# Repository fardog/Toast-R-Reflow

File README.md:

# Toast-R-Reflow

This is a fork of [nsayer/Toast-R-Reflow][fork] but:

* Only the Controller II is supported
* Firmware builds with [PlatformIO][]
* Eagle files converted to KiCAD (untested, unfixed, and definitely missing
  things)

[fork]: https://github.com/nsayer/Toast-R-Reflow
[PlatformIO]: https://platformio.org/

I take credit for none of this; it's just more convenient for me to make changes
to the firmware this way, and the only reason I converted the hardware to KiCAD
is because that's what I had available to view them.

Included here is what it'll take to get firmware building and uploading using
this repo. The [original README][] has been moved to `README-original.md`.

Just don't blame me if you donk your board; I don't know what I'm doing.

[original README]: ./README-original.md

## Preparing for custom firmware

It's easiest to use PlatformIO once the board can be detected as an Arduino, so
you'll need to burn a bootloader.

What's required to do so isn't outlined in detail here, but here's what you'll
need to know:

* The ICSP header is the blue header on the back of the unit; listed as `JP4`,
  near the open-source hardware logo
* Its pinout is the usual ICSP layout; left-to-right, top-to-bottom:
  * Reset
  * SCK
  * MISO
  * GND
  * MOSI
  * VCC (5v)
* It runs an Atmega328PB, and is 5v tolerant
* I used an Arduino Micro as an ISP without issue, with reset wired to digital
  pin 10

The original README says that the board would work fine if you pretend it's an
Arduino UNO; that just didn't work for me given that board is an Atmega328P, and
this is an Atmega328PB. I read they're maybe mostly compatible but without
finding anything difinitive there, I got it working as the PB model.

For a bootloader that supports the Atmega328PB, use [MiniCore][]. Follow its
instructions to burn the loader; I used settings:

* Board: MiniCore -> Atmega328
* Clock: External 16 MHz
* BOD: BOD2.7V
* EEPROM: EEPROM retained
* Compiler LTO: LTO disabled
* Variant: 328PB
* Bootloader: Yes (UART0)

[MiniCore]: https://github.com/MCUdude/MiniCore

## FTDI Header

The board has a 6-pin inline header labeled "FTDI" which can be used for
programming, but you need to solder the jumper pins (labeled `SJ1`) to activate
the reset line. In my case, it was also missing a 0.1uF capacitor `C10` on the
line, but I have to assume that's not a common error.

## Building Custom Firmware

The `platformio.ini` in this repo is set up correctly; building and uploading
the firmware should work without additional settings.

## Changes to the firmware

* `SiO2` profile for drying silica gel; 110°C for 3hr

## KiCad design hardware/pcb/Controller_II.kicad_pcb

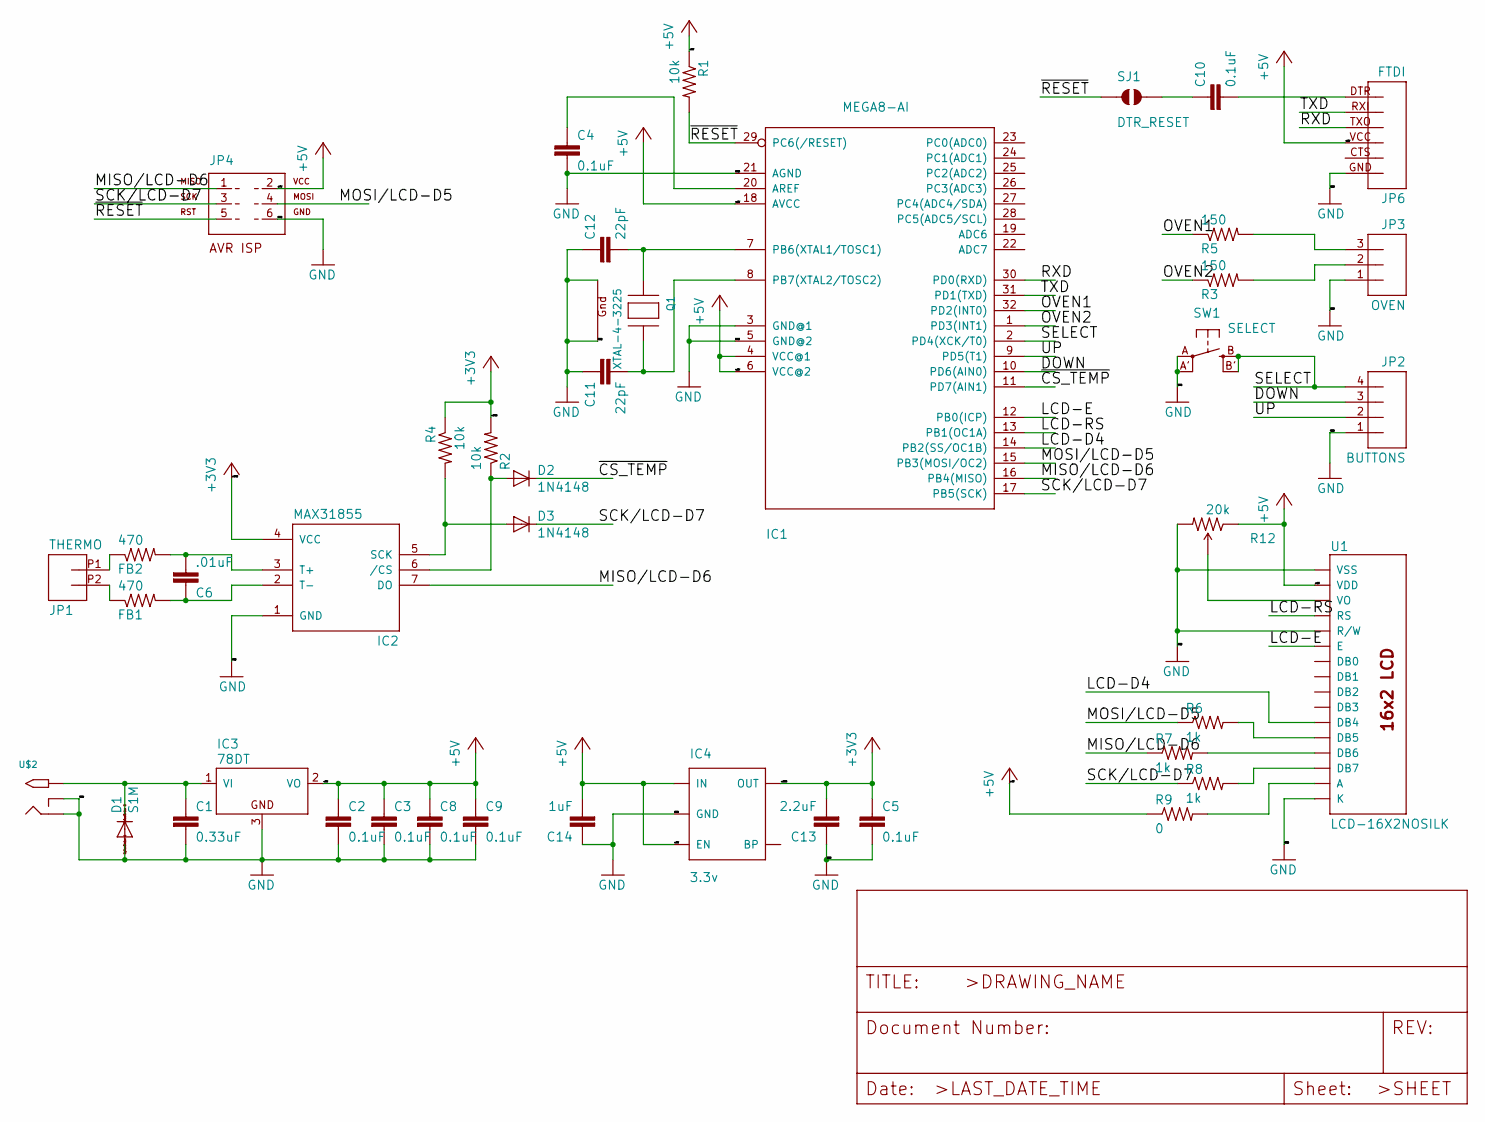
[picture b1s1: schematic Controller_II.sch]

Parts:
C1: 0.33uF; 0805
C2, C3, C4, C5, C8, C9, C10: 0.1uF; 0805
C6: .01uF; 0805
C11, C12: 22pF; 0805
C13: 2.2uF; 0805
C14: 1uF; 0805
D1: S1M; DO-214AC
D2, D3: 1N4148; SOD-323
FB1, FB2: 470; 0805
IC1: MEGA8-AI; TQFP32-08
IC2: MAX31855; SO08
IC3: 78DT; TO252
IC4: 3.3v; SOT23-5
JP1: THERMO; 1X02_2.54_SCREWTERM
JP2: BUTTONS; 1X04
JP3: OVEN; SCREWTERMINAL-5MM-3
JP4: ISP; AVR-ISP-6
JP6: FTDI; FTDI_BASIC
Q1: XTAL-4-3225; NX3225
R1, R2, R4: 10k; 0805
R3, R5: 150; 0805
R6, R7, R8: 1k; 0805
R9: 0; 0805
R12: 20k; TRIMPOT-3MM
SJ1: DTR_RESET; SJ_2S-NO
SW1: SELECT; EVQ-Q2
U1: LCD-16X2NOSILK; LCD-16X2_NOSILK
U$2: 2.1MMJACKSMT; DCJACK_2MM_SMT

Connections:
+3V3: C5.1, C13.2, IC2.4 (VCC), IC4.5 (OUT), R2.2, R4.1
+5V: C2.1, C3.1, C8.1, C9.1, C14.2, IC1.4 (VCC@1), IC1.6 (VCC@2), IC1.18 (AVCC), IC3.2 (VO), IC4.1 (IN), IC4.3 (EN), JP4.2, JP6.VCC (4), R1.1, R9.1, R12.1 (CCW), U1.2 (VDD)
/DOWN: IC1.10 (PD6(AIN0)), JP2.3
/LCD-D4: IC1.14 (PB2(SS/OC1B)), U1.11 (DB4)
/LCD-E: IC1.12 (PB0(ICP)), U1.6 (E)
/LCD-RS: IC1.13 (PB1(OC1A)), U1.4 (RS)
/MISO/LCD-D6: IC1.16 (PB4(MISO)), IC2.7 (DO), JP4.1, R7.1
/MOSI/LCD-D5: IC1.15 (PB3(MOSI/OC2)), JP4.4, R6.1
/OVEN1: IC1.32 (PD2(INT0)), R5.1
/OVEN2: IC1.1 (PD3(INT1)), R3.1
/RXD: IC1.30 (PD0(RXD)), JP6.TXO (3)
/SCK/LCD-D7: D3.1 (C), IC1.17 (PB5(SCK)), JP4.3, R8.1
/SELECT: IC1.2 (PD4(XCK/T0)), JP2.4, SW1.B (S), SW1.B' (S1)
/TXD: IC1.31 (PD1(TXD)), JP6.RXI (2)
/UP: IC1.9 (PD5(T1)), JP2.2
/~CS_TEMP: D2.1 (C), IC1.11 (PD7(AIN1))
/~RESET: IC1.29 (PC6(/RESET)), JP4.5, R1.2, SJ1.1
GND: C1.2, C2.2, C3.2, C4.2, C5.2, C8.2, C9.2, C11.1, C12.1, C13.1, C14.1, D1.A, IC1.3 (GND@1), IC1.5 (GND@2), IC1.21 (AGND), IC2.1 (GND), IC3.3 (GND), IC4.2 (GND), JP2.1, JP3.1, JP4.6, JP6.GND (6), Q1.2 (G2), Q1.4 (G1), R12.3 (CW), SW1.A, SW1.A' (P1), U1.1 (VSS), U1.5 (R/W), U1.16 (K), U$2.GND (RING), U$2.GNDBREAK (RING_SW)
unnamed: C1.1, D1.C, IC3.1 (VI), U$2.PWR1 (TIP), U$2.PWR2 (TIP)
unnamed: C4.1, IC1.20 (AREF)
unnamed: C6.1, FB1.2, IC2.2 (T-)
unnamed: C6.2, FB2.2, IC2.3 (T+)
unnamed: C10.1, SJ1.2
unnamed: C10.2, JP6.DTR (1)
unnamed: C11.2, IC1.8 (PB7(XTAL2/TOSC2)), Q1.3 (X2)
unnamed: C12.2, IC1.7 (PB6(XTAL1/TOSC1)), Q1.1 (X1)
unnamed: D2.2 (A), IC2.6 (/CS), R2.1
unnamed: D3.2 (A), IC2.5 (SCK), R4.2
unnamed: FB1.1, JP1.P2 (2)
unnamed: FB2.1, JP1.P1 (1)
unnamed: JP3.2, R3.2
unnamed: JP3.3, R5.2
unnamed: R6.2, U1.12 (DB5)
unnamed: R7.2, U1.13 (DB6)
unnamed: R8.2, U1.14 (DB7)
unnamed: R9.2, U1.15 (A)
unnamed: R12.2 (WIPER), U1.3 (VO)

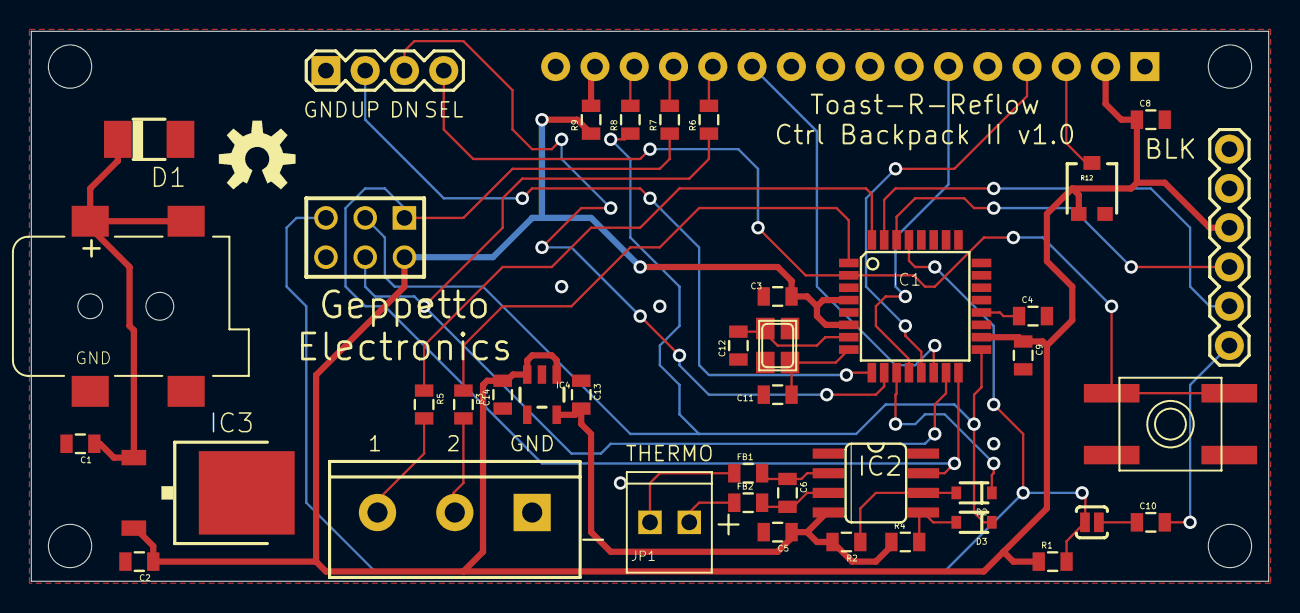
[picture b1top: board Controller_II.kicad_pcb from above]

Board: 6 copper layers, 80.0 x 35.6 mm, 43 parts (0 on the bottom side), 37 nets.

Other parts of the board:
U$1: OSHW-LOGO-M

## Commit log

2021-08-17 build on platformio
2021-08-17 ftdi settings
2021-08-20 fix chip type
2021-08-20 move original README
2021-08-21 add new profile, add README
